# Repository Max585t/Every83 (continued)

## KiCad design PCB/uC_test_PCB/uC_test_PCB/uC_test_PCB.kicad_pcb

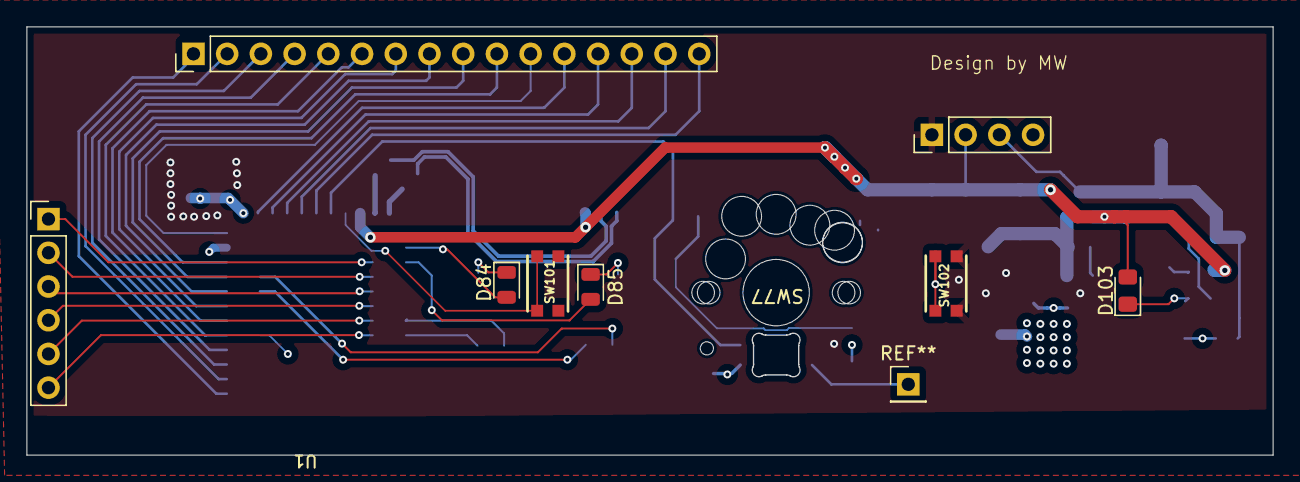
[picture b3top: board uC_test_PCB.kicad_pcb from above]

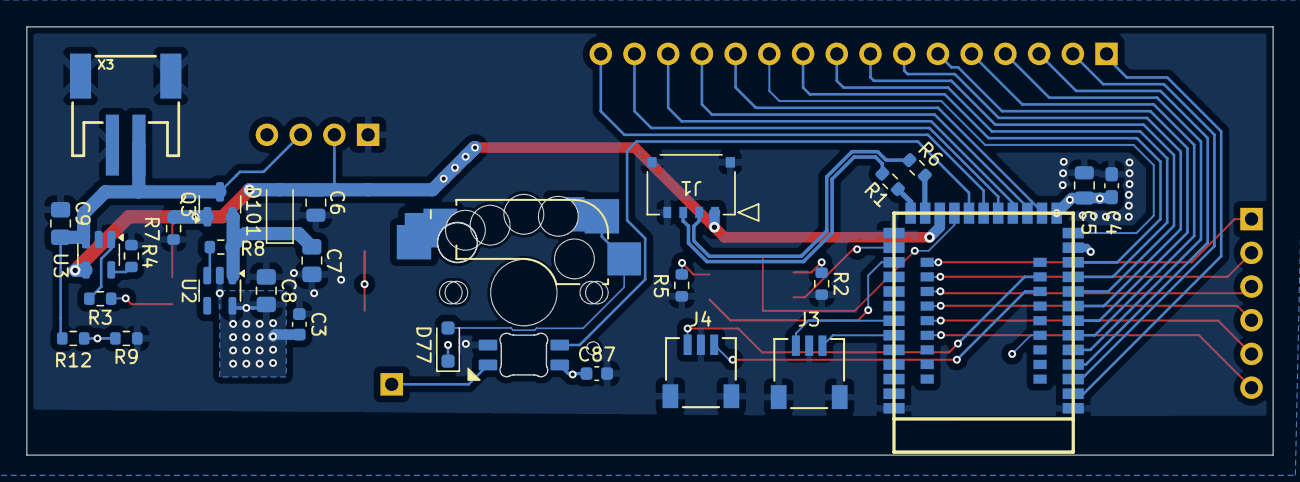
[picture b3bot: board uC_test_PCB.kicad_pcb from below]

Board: 4 copper layers, 93.9 x 32.3 mm, 34 parts (27 on the bottom side), 2 nets.

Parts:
C3: 0.1uF; C_0603_1608Metric
C4: 0.1uF; C_0603_1608Metric_Pad1.08x0.95mm_HandSolder
C5, C6: 10uF; C_0805_2012Metric
C7, C8, C9: 10uF; C_0805_2012Metric_Pad1.18x1.45mm_HandSolder
C87: C; C_0603_1608Metric
D77: D; D_SOD-323_HandSoldering
D84, D85: LED; LED_0805_2012Metric
D101: MBR120; D_SOD-123
D103: LED; D_0805_2012Metric_Pad1.15x1.40mm_HandSolder
J1: 781710004; CON_781710004
J3, J4: SM03B-SRSS-TB; CONN_SM03B-SRSS-TB_JST
Q3: DMG2305; SOT-23
R1, R6: 22R; R_0603_1608Metric
R2, R3, R5: 1K; R_0603_1608Metric
R4: 4.7K; R_0603_1608Metric
R7, R8, R9, R12: 100k; R_0603_1608Metric
SW77: gateron-ks27-choc-v1-mx-hotswap
SW101, SW102: KMR2; BTN_KMR2_4.6X2.8
U1: Core52840
U2: AP2112(3.3V); SOT-23-5
U3: MCP73831T-2ACI/OT; SOT-23-5
X3: JSTPH; JSTPH2

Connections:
3v3: C3.2, C4.2, C5.2, C8.2, C87.1, SW77.4 (VDD), U1.55 (VREF), U2.5 (OUT)
GND: C3.1, C4.1, C5.1, C6.1, C7.1, C8.1, C9.1, C87.2, J1.4, J1.5, J1.6, J3.2, J3.4, J3.5, J4.2, J4.4, J4.5, R2.2, R4.2, R5.2, R7.2, R9.2, SW77.6 (GND), SW102.A, SW102.A' (P1), U1.1 (GND), U1.32 (GND), U1.44 (GND), U2.2 (GND), U3.2 (VSS), X3.1, X3.NC1, X3.NC2

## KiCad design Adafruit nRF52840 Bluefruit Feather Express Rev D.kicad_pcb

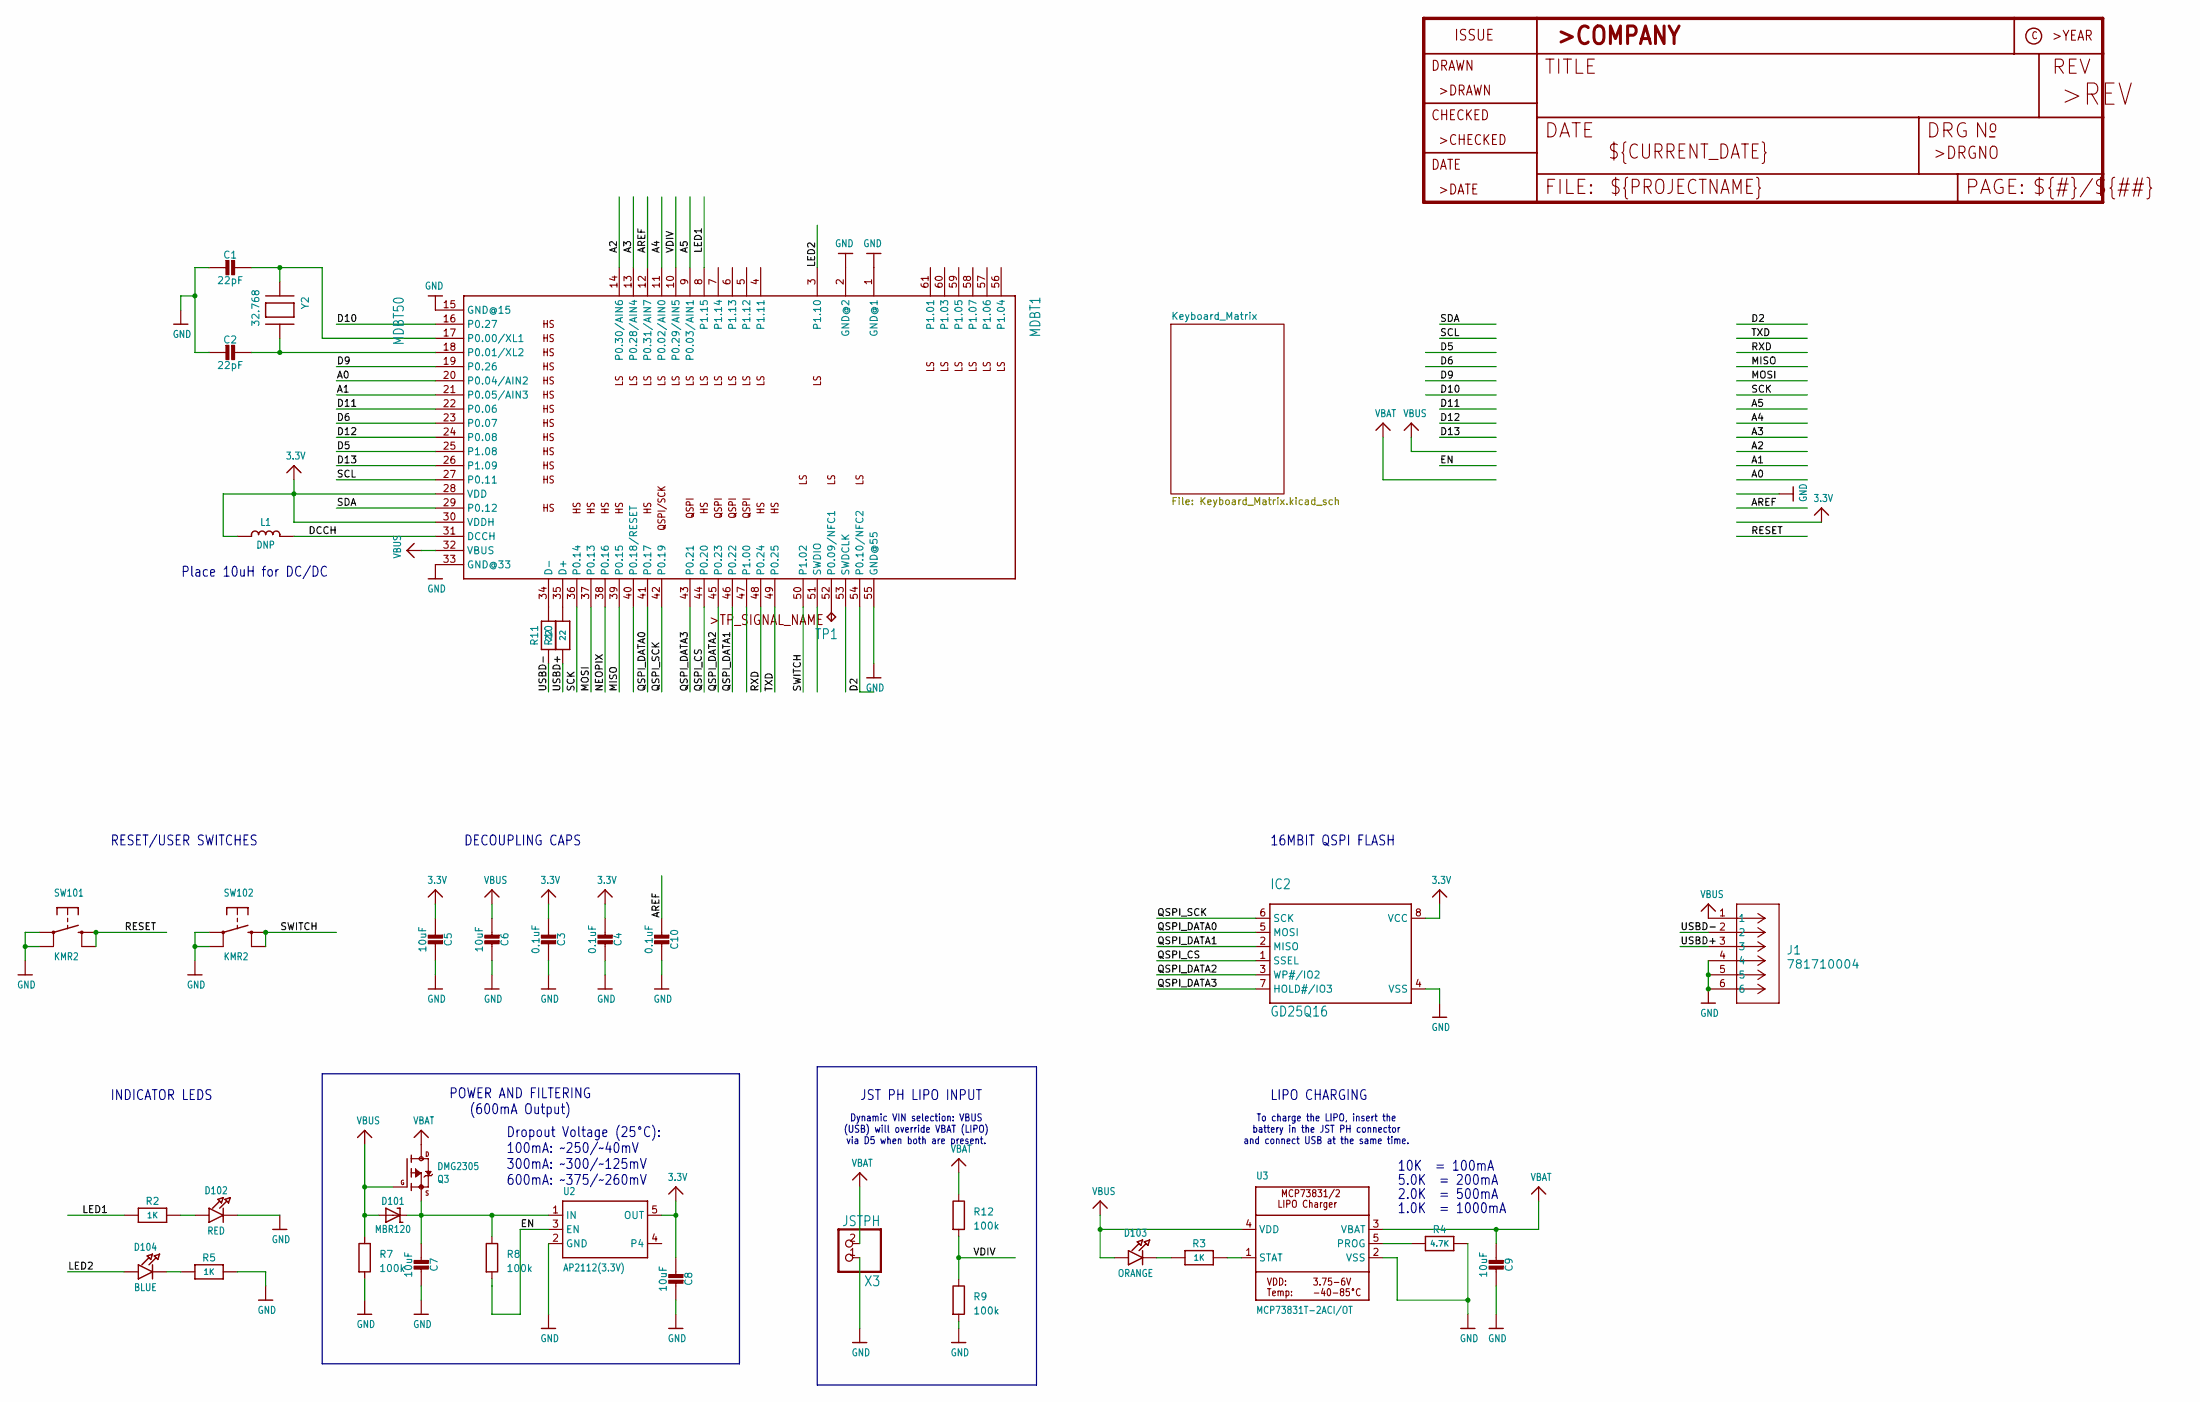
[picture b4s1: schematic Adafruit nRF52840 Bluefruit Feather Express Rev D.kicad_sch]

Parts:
C1, C2: 22pF; 0603-NO
C3, C4, C10: 0.1uF; 0603-NO
C5, C6, C7, C8, C9: 10uF; 0805-NO
D101: MBR120; SOD-123
D102: RED; CHIPLED_0805_NOOUTLINE
D103: ORANGE; CHIPLED_0805_NOOUTLINE
D104: BLUE; CHIPLED_0805_NOOUTLINE
IC2: GD25Q16; USON8
J1: 781710004; CON_781710004
L1: DNP; _0805MP
MDBT1: MDBT50
Q3: DMG2305; SOT23-R
R2, R3, R5: 1K; 0603-NO
R4: 4.7K; 0603-NO
R7, R8, R9, R12: 100k; R_0603_1608Metric
R10, R11: 22; 0603-NO
SW101, SW102: KMR2; BTN_KMR2_4.6X2.8
TP1: TPTP10R; TP10R
U2: AP2112(3.3V); SOT23-5
U3: MCP73831T-2ACI/OT; SOT23-5
X3: JSTPH; JSTPH2
Y2: 32.768; XTAL3215

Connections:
3.3V: C3.2, C4.2, C5.2, C8.2, IC2.8 (VCC), L1.1, MDBT1.28 (VDD), MDBT1.30 (VDDH), U2.5 (OUT); also elsewhere on the board
/A0: MDBT1.20 (P0.04/AIN2)
/A1: MDBT1.21 (P0.05/AIN3)
/A2: MDBT1.14 (P0.30/AIN6)
/A3: MDBT1.13 (P0.28/AIN4)
/A4: MDBT1.11 (P0.02/AIN0)
/A5: MDBT1.9 (P0.03/AIN1)
/AREF: C10.2, MDBT1.12 (P0.31/AIN7)
/D2: MDBT1.54 (P0.10/NFC2)
/D5: MDBT1.25 (P1.08)
/D6: MDBT1.23 (P0.07)
/D9: MDBT1.19 (P0.26)
/D10: MDBT1.16 (P0.27)
/D11: MDBT1.22 (P0.06)
/D12: MDBT1.24 (P0.08)
/D13: MDBT1.26 (P1.09)
/DCCH: L1.2, MDBT1.31 (DCCH)
/EN: R8.2, U2.3 (EN)
/LED1: MDBT1.8 (P1.15), R2.1
/LED2: D104.A, MDBT1.3 (P1.10)
/MISO: MDBT1.39 (P0.15)
/MOSI: MDBT1.37 (P0.13)
/NEOPIX: MDBT1.38 (P0.16)
/QSPI_CS: IC2.1 (SSEL), MDBT1.44 (P0.20)
/QSPI_DATA0: IC2.5 (MOSI), MDBT1.41 (P0.17)
/QSPI_DATA1: IC2.2 (MISO), MDBT1.46 (P0.22)
/QSPI_DATA2: IC2.3 (WP#/IO2), MDBT1.45 (P0.23)
/QSPI_DATA3: IC2.7 (HOLD#/IO3), MDBT1.43 (P0.21)
/QSPI_SCK: IC2.6 (SCK), MDBT1.42 (P0.19)
/RESET: SW101.B (S), SW101.B' (S1)
/RXD: MDBT1.48 (P0.24)
/SCK: MDBT1.36 (P0.14)
/SCL: MDBT1.27 (P0.11)
/SDA: MDBT1.29 (P0.12)
/SWITCH: MDBT1.50 (P1.02), SW102.B (S), SW102.B' (S1)
/TXD: MDBT1.49 (P0.25)
/USBD+: J1.3, R10.1
/USBD-: J1.2, R11.1
/VDIV: MDBT1.10 (P0.29/AIN5), R9.1, R12.2
GND: C1.2, C2.2, C3.1, C4.1, C5.1, C6.1, C7.1, C8.1, C9.1, C10.1, D102.C, IC2.4 (VSS), J1.4, J1.5, J1.6, MDBT1.1 (GND@1), MDBT1.2 (GND@2), MDBT1.15 (GND@15), MDBT1.33 (GND@33), MDBT1.55 (GND@55), R4.2, R5.2, R7.2, R9.2, SW101.A, SW101.A' (P1), SW102.A, SW102.A' (P1), U2.2 (GND), U3.2 (VSS), X3.1; also elsewhere on the board
unnamed: D102.A, R2.2
unnamed: D103.C, R3.1
unnamed: D104.C, R5.1
unnamed: MDBT1.35 (D+), R10.2
unnamed: MDBT1.34 (D-), R11.2
unnamed: C1.1, MDBT1.17 (P0.00/XL1), Y2.P$1
unnamed: C2.1, MDBT1.18 (P0.01/XL2), Y2.P$2
unnamed: MDBT1.52 (P0.09/NFC1), TP1.TP
unnamed: C7.2, D101.C, Q3.2 (S), R8.1, U2.1 (IN)
unnamed: R4.1, U3.5 (PROG)
unnamed: R3.2, U3.1 (STAT)
VBAT: C9.2, Q3.3 (D), R12.1, U3.3 (VBAT), X3.2
VBUS: C6.2, D101.A, D103.A, J1.1, MDBT1.32 (VBUS), Q3.1 (G), R7.1, U3.4 (VDD)

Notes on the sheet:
Dynamic VIN selection: VBUS (USB) will override VBAT (LIPO) via D5 when both are present.
To charge the LIPO, insert the battery in the JST PH connector and connect USB at the same time.
POWER AND FILTERING (600mA Output)
1.0K = 1000mA
Place 10uH for DC/DC
INDICATOR LEDS
5.0K = 200mA
JST PH LIPO INPUT
LIPO CHARGING
RESET/USER SWITCHES
10K = 100mA
2.0K = 500mA
16MBIT QSPI FLASH
Dropout Voltage (25°C): 100mA: ~250/~40mV 300mA: ~300/~125mV 600mA: ~375/~260mV
DECOUPLING CAPS

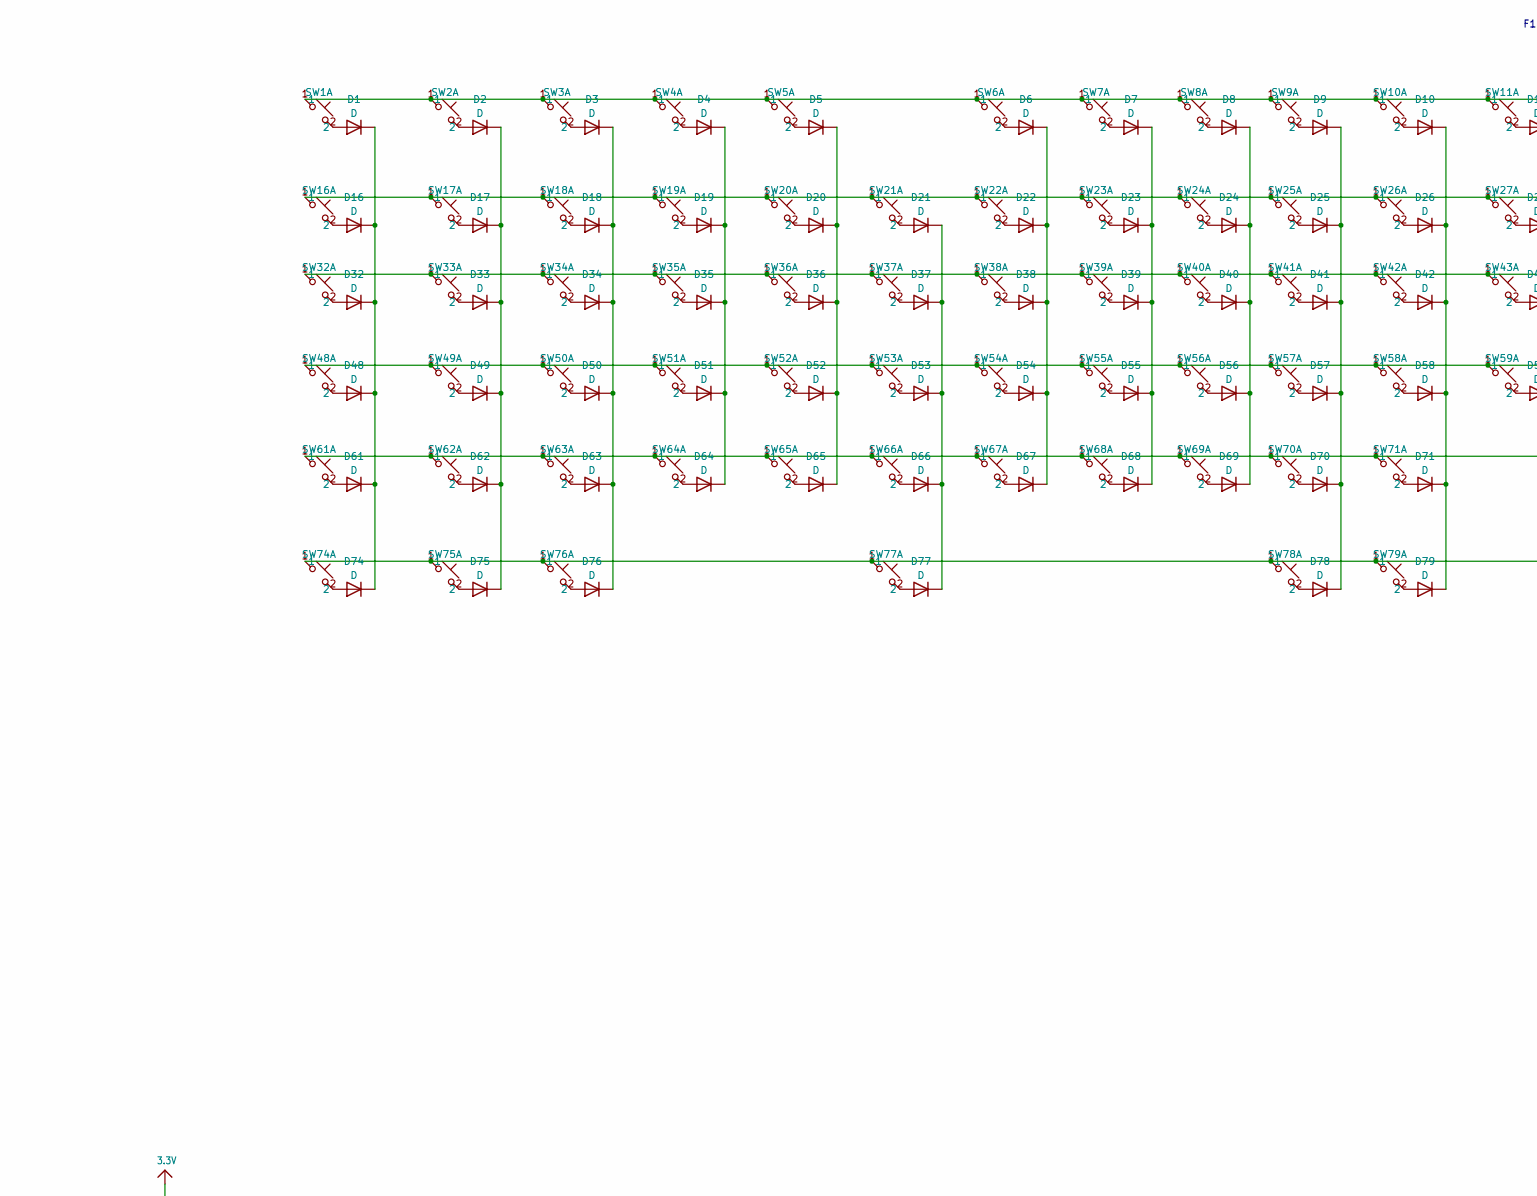
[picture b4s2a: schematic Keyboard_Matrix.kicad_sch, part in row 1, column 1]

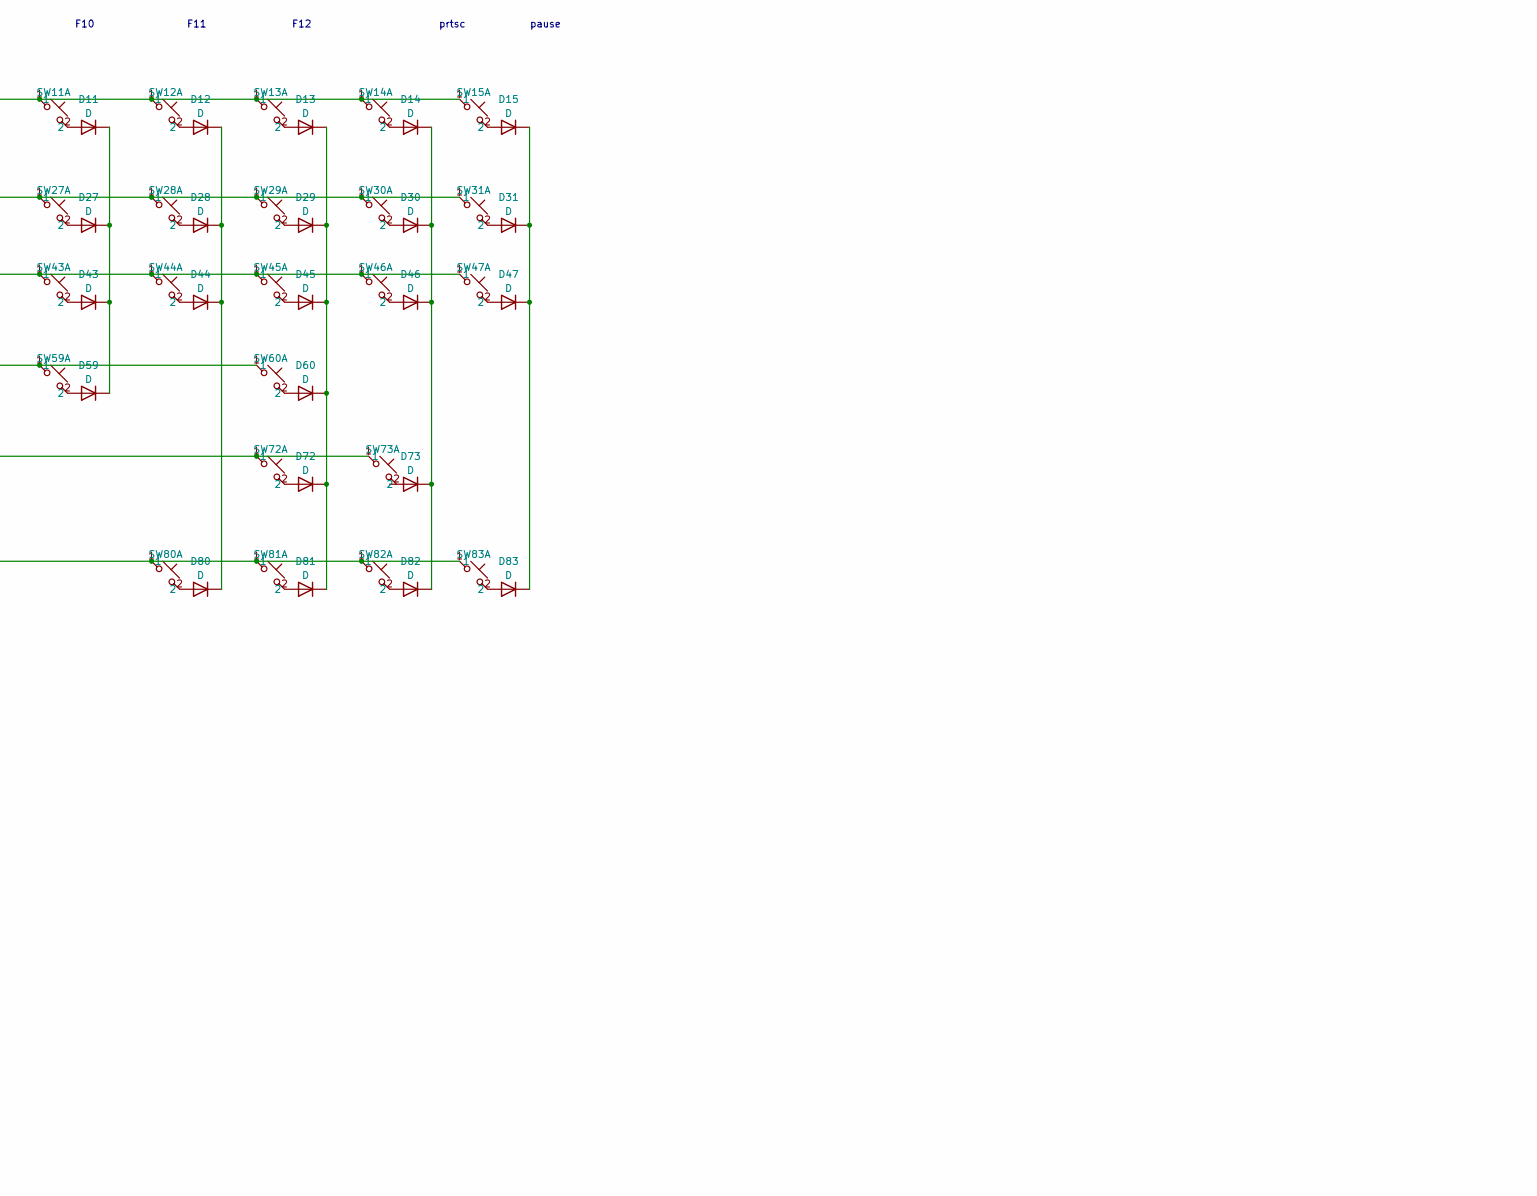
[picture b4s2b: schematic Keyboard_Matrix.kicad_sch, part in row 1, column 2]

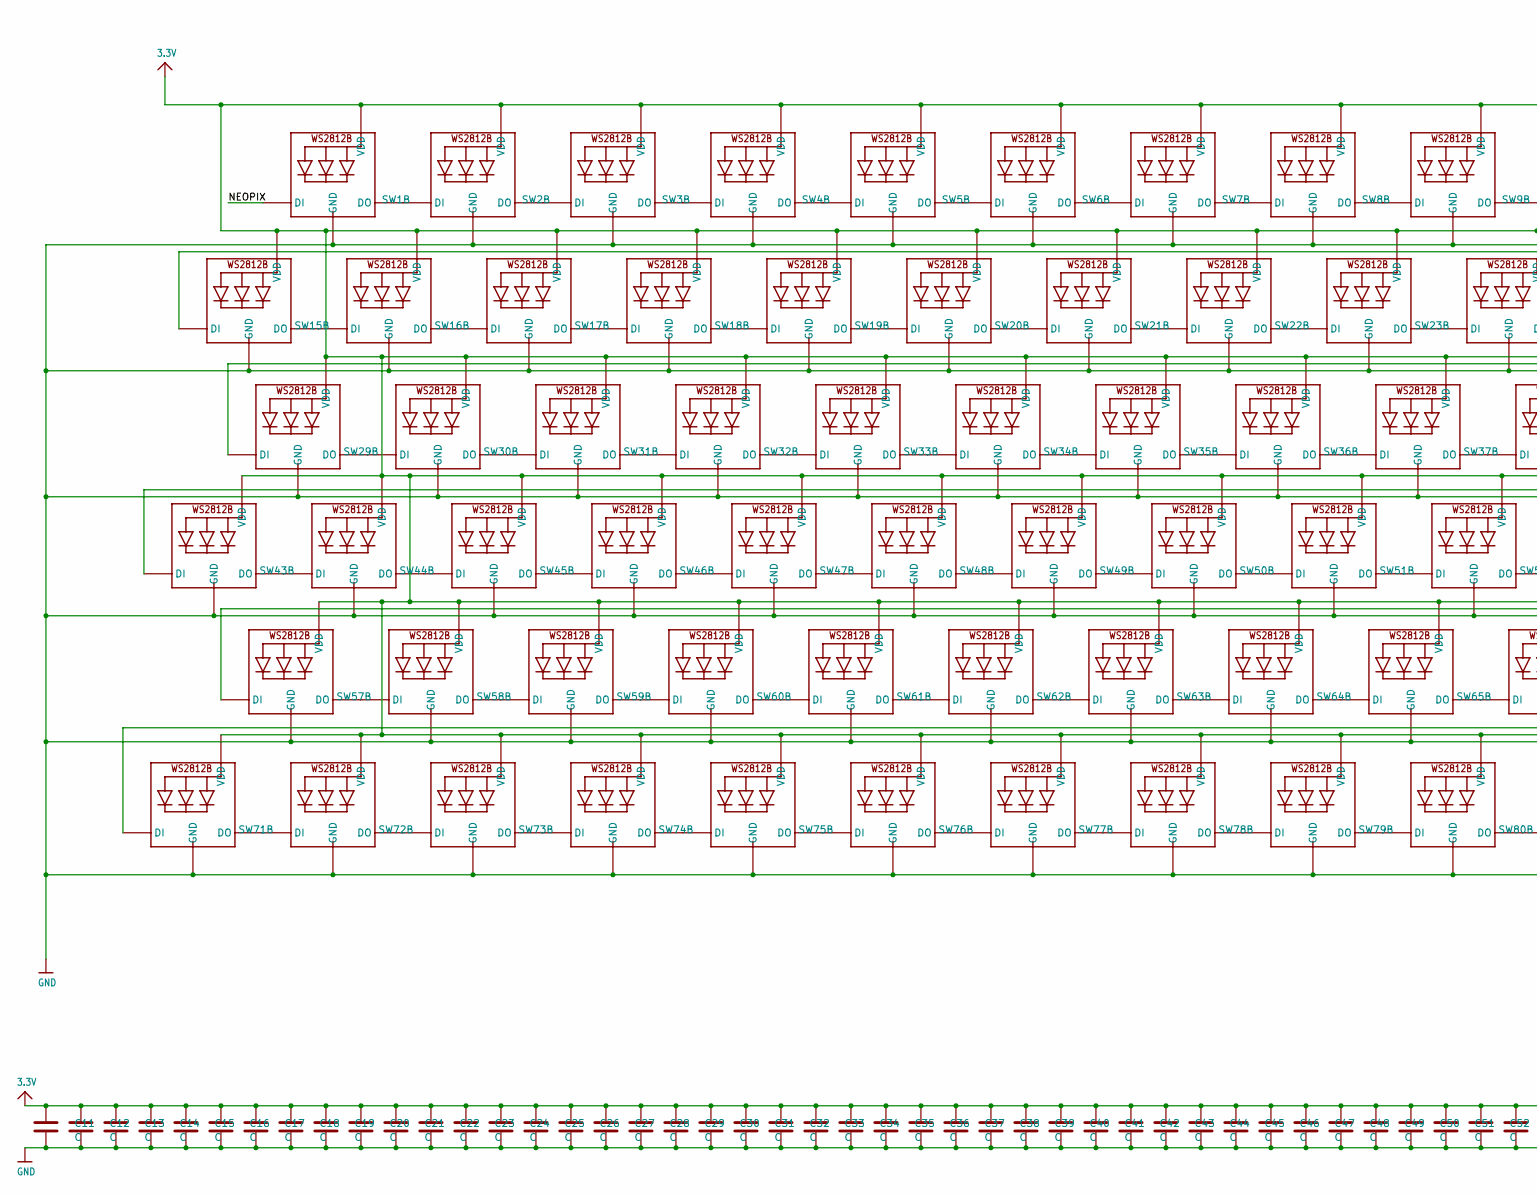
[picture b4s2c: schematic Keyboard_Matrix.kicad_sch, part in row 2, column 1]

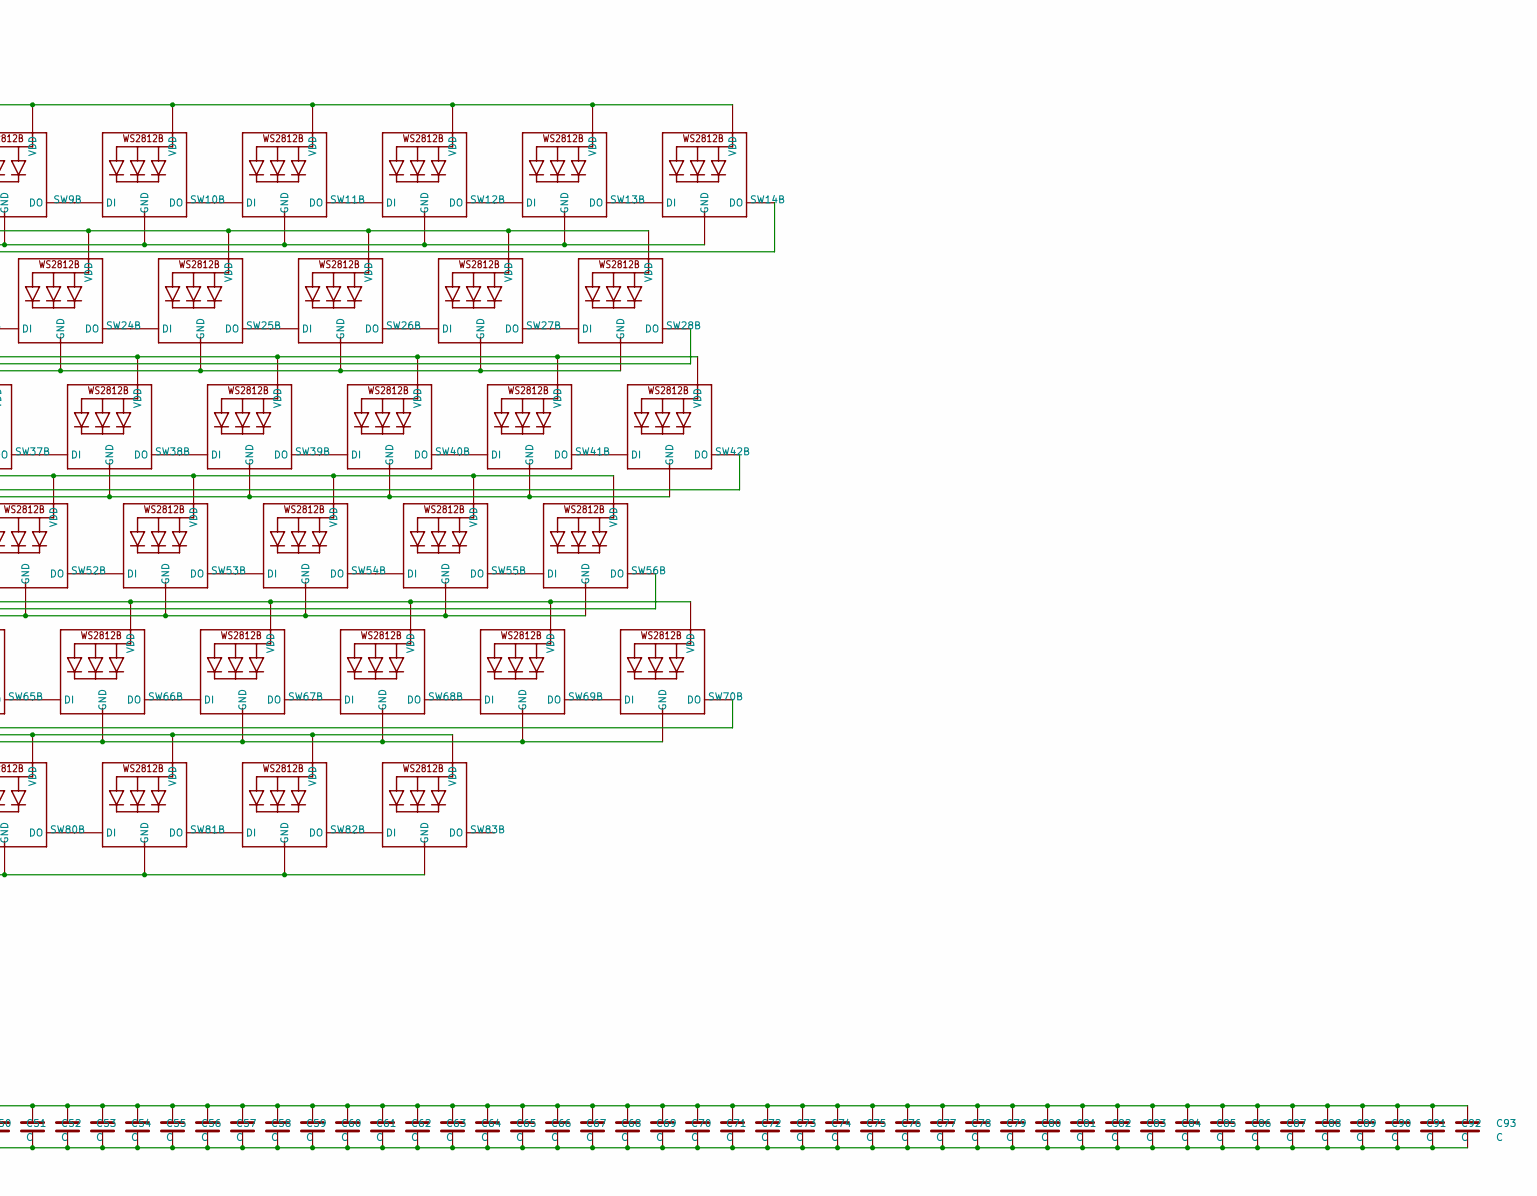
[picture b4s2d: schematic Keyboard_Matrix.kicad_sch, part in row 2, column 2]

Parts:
C11, C12, C13, C14, C15, C16, C17, C18, C19, C20, C21, C22, C23, C24, C25, C26, C27, C28, C29, C30, C31, C32, C33, C34, C35, C36, C37, C38, C39, C40, C41, C42, C43, C44, C45, C46, C47, C48, C49, C50, C51, C52, C53, C54, C55, C56, C57, C58, C59, C60, C61, C62, C63, C64, C65, C66, C67, C68, C69, C70, C71, C72, C73, C74, C75, C76, C77, C78, C79, C80, C81, C82, C83, C84, C85, C86, C87, C88, C89, C90, C91, C92, C93: C; C_0603_1608Metric
D1, D2, D3, D4, D5, D6, D7, D8, D9, D10, D11, D12, D13, D14, D15, D16, D17, D18, D19, D20, D21, D22, D23, D24, D25, D26, D27, D28, D29, D30, D31, D32, D33, D34, D35, D36, D37, D38, D39, D40, D41, D42, D43, D44, D45, D46, D47, D48, D49, D50, D51, D52, D53, D54, D55, D56, D57, D58, D59, D60, D61, D62, D63, D64, D65, D66, D67, D68, D69, D70, D71, D72, D73, D74, D75, D76, D77, D78, D79, D80, D81, D82, D83: D; D_SOD-323_HandSoldering
SW1, SW2, SW3, SW4, SW5, SW6, SW7, SW8, SW9, SW10, SW11, SW12, SW13, SW14, SW15, SW16, SW17, SW18, SW19, SW20, SW21, SW22, SW23, SW24, SW25, SW26, SW27, SW28, SW29, SW30, SW31, SW32, SW33, SW34, SW35, SW36, SW37, SW38, SW39, SW40, SW41, SW42, SW43, SW44, SW45, SW46, SW47, SW48, SW49, SW50, SW51, SW52, SW53, SW54, SW55, SW56, SW57, SW58, SW59, SW60, SW61, SW62, SW63, SW64, SW65, SW66, SW67, SW68, SW69, SW70, SW71, SW72, SW73, SW74, SW75, SW76, SW77, SW78, SW79, SW80, SW81, SW82, SW83: gateron-ks27-choc-v1-mx-hotswap

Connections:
3.3V: C11.1, C12.1, C13.1, C14.1, C15.1, C16.1, C17.1, C18.1, C19.1, C20.1, C21.1, C22.1, C23.1, C24.1, C25.1, C26.1, C27.1, C28.1, C29.1, C30.1, C31.1, C32.1, C33.1, C34.1, C35.1, C36.1, C37.1, C38.1, C39.1, C40.1, C41.1, C42.1, C43.1, C44.1, C45.1, C46.1, C47.1, C48.1, C49.1, C50.1, C51.1, C52.1, C53.1, C54.1, C55.1, C56.1, C57.1, C58.1, C59.1, C60.1, C61.1, C62.1, C63.1, C64.1, C65.1, C66.1, C67.1, C68.1, C69.1, C70.1, C71.1, C72.1, C73.1, C74.1, C75.1, C76.1, C77.1, C78.1, C79.1, C80.1, C81.1, C82.1, C83.1, C84.1, C85.1, C86.1, C87.1, C88.1, C89.1, C90.1, C91.1, C92.1, C93.1, SW1.4 (VDD), SW2.4 (VDD), SW3.4 (VDD), SW4.4 (VDD), SW5.4 (VDD), SW6.4 (VDD), SW7.4 (VDD), SW8.4 (VDD), SW9.4 (VDD), SW10.4 (VDD), SW11.4 (VDD), SW12.4 (VDD), SW13.4 (VDD), SW14.4 (VDD), SW15.4 (VDD), SW16.4 (VDD), SW17.4 (VDD), SW18.4 (VDD), SW19.4 (VDD), SW20.4 (VDD), SW21.4 (VDD), SW22.4 (VDD), SW23.4 (VDD), SW24.4 (VDD), SW25.4 (VDD), SW26.4 (VDD), SW27.4 (VDD), SW28.4 (VDD), SW29.4 (VDD), SW30.4 (VDD), SW31.4 (VDD), SW32.4 (VDD), SW33.4 (VDD), SW34.4 (VDD), SW35.4 (VDD), SW36.4 (VDD), SW37.4 (VDD), SW38.4 (VDD), SW39.4 (VDD), SW40.4 (VDD), SW41.4 (VDD), SW42.4 (VDD), SW43.4 (VDD), SW44.4 (VDD), SW45.4 (VDD), SW46.4 (VDD), SW47.4 (VDD), SW48.4 (VDD), SW49.4 (VDD), SW50.4 (VDD), SW51.4 (VDD), SW52.4 (VDD), SW53.4 (VDD), SW54.4 (VDD), SW55.4 (VDD), SW56.4 (VDD), SW57.4 (VDD), SW58.4 (VDD), SW59.4 (VDD), SW60.4 (VDD), SW61.4 (VDD), SW62.4 (VDD), SW63.4 (VDD), SW64.4 (VDD), SW65.4 (VDD), SW66.4 (VDD), SW67.4 (VDD), SW68.4 (VDD), SW69.4 (VDD), SW70.4 (VDD), SW71.4 (VDD), SW72.4 (VDD), SW73.4 (VDD), SW74.4 (VDD), SW75.4 (VDD), SW76.4 (VDD), SW77.4 (VDD), SW78.4 (VDD), SW79.4 (VDD), SW80.4 (VDD), SW81.4 (VDD), SW82.4 (VDD), SW83.4 (VDD); also elsewhere on the board
/Keyboard_Matrix/NEOPIX: SW1.3 (DI)
GND: C11.2, C12.2, C13.2, C14.2, C15.2, C16.2, C17.2, C18.2, C19.2, C20.2, C21.2, C22.2, C23.2, C24.2, C25.2, C26.2, C27.2, C28.2, C29.2, C30.2, C31.2, C32.2, C33.2, C34.2, C35.2, C36.2, C37.2, C38.2, C39.2, C40.2, C41.2, C42.2, C43.2, C44.2, C45.2, C46.2, C47.2, C48.2, C49.2, C50.2, C51.2, C52.2, C53.2, C54.2, C55.2, C56.2, C57.2, C58.2, C59.2, C60.2, C61.2, C62.2, C63.2, C64.2, C65.2, C66.2, C67.2, C68.2, C69.2, C70.2, C71.2, C72.2, C73.2, C74.2, C75.2, C76.2, C77.2, C78.2, C79.2, C80.2, C81.2, C82.2, C83.2, C84.2, C85.2, C86.2, C87.2, C88.2, C89.2, C90.2, C91.2, C92.2, C93.2, SW1.6 (GND), SW2.6 (GND), SW3.6 (GND), SW4.6 (GND), SW5.6 (GND), SW6.6 (GND), SW7.6 (GND), SW8.6 (GND), SW9.6 (GND), SW10.6 (GND), SW11.6 (GND), SW12.6 (GND), SW13.6 (GND), SW14.6 (GND), SW15.6 (GND), SW16.6 (GND), SW17.6 (GND), SW18.6 (GND), SW19.6 (GND), SW20.6 (GND), SW21.6 (GND), SW22.6 (GND), SW23.6 (GND), SW24.6 (GND), SW25.6 (GND), SW26.6 (GND), SW27.6 (GND), SW28.6 (GND), SW29.6 (GND), SW30.6 (GND), SW31.6 (GND), SW32.6 (GND), SW33.6 (GND), SW34.6 (GND), SW35.6 (GND), SW36.6 (GND), SW37.6 (GND), SW38.6 (GND), SW39.6 (GND), SW40.6 (GND), SW41.6 (GND), SW42.6 (GND), SW43.6 (GND), SW44.6 (GND), SW45.6 (GND), SW46.6 (GND), SW47.6 (GND), SW48.6 (GND), SW49.6 (GND), SW50.6 (GND), SW51.6 (GND), SW52.6 (GND), SW53.6 (GND), SW54.6 (GND), SW55.6 (GND), SW56.6 (GND), SW57.6 (GND), SW58.6 (GND), SW59.6 (GND), SW60.6 (GND), SW61.6 (GND), SW62.6 (GND), SW63.6 (GND), SW64.6 (GND), SW65.6 (GND), SW66.6 (GND), SW67.6 (GND), SW68.6 (GND), SW69.6 (GND), SW70.6 (GND), SW71.6 (GND), SW72.6 (GND), SW73.6 (GND), SW74.6 (GND), SW75.6 (GND), SW76.6 (GND), SW77.6 (GND), SW78.6 (GND), SW79.6 (GND), SW80.6 (GND), SW81.6 (GND), SW82.6 (GND), SW83.6 (GND); also elsewhere on the board
unnamed: D1.2 (A), SW1.2
unnamed: D1.1 (K), D16.1 (K), D32.1 (K), D48.1 (K), D61.1 (K), D74.1 (K)
unnamed: D2.2 (A), SW2.2
unnamed: D3.2 (A), SW3.2
unnamed: D4.2 (A), SW4.2
unnamed: D5.2 (A), SW5.2
unnamed: D6.2 (A), SW6.2
unnamed: D7.2 (A), SW7.2
unnamed: D8.2 (A), SW8.2
unnamed: D9.2 (A), SW9.2
unnamed: D10.2 (A), SW10.2
unnamed: D10.1 (K), D26.1 (K), D42.1 (K), D58.1 (K), D71.1 (K), D79.1 (K)
unnamed: D11.2 (A), SW11.2
unnamed: D11.1 (K), D27.1 (K), D43.1 (K), D59.1 (K)
unnamed: D12.2 (A), SW12.2
unnamed: D12.1 (K), D28.1 (K), D44.1 (K), D80.1 (K)
unnamed: D13.2 (A), SW13.2
unnamed: D13.1 (K), D29.1 (K), D45.1 (K), D60.1 (K), D72.1 (K), D81.1 (K)
unnamed: D14.2 (A), SW14.2
unnamed: D14.1 (K), D30.1 (K), D46.1 (K), D73.1 (K), D82.1 (K)
unnamed: D15.2 (A), SW15.2
unnamed: D15.1 (K), D31.1 (K), D47.1 (K), D83.1 (K)
unnamed: D16.2 (A), SW16.2
unnamed: D17.2 (A), SW17.2
unnamed: D2.1 (K), D17.1 (K), D33.1 (K), D49.1 (K), D62.1 (K), D75.1 (K)
unnamed: D18.2 (A), SW18.2
unnamed: D3.1 (K), D18.1 (K), D34.1 (K), D50.1 (K), D63.1 (K), D76.1 (K)
unnamed: D19.2 (A), SW19.2
unnamed: D4.1 (K), D19.1 (K), D35.1 (K), D51.1 (K), D64.1 (K)
unnamed: D20.2 (A), SW20.2
unnamed: D5.1 (K), D20.1 (K), D36.1 (K), D52.1 (K), D65.1 (K)
unnamed: D21.2 (A), SW21.2
unnamed: D21.1 (K), D37.1 (K), D53.1 (K), D66.1 (K), D77.1 (K)
unnamed: D22.2 (A), SW22.2
unnamed: D6.1 (K), D22.1 (K), D38.1 (K), D54.1 (K), D67.1 (K)
unnamed: D23.2 (A), SW23.2
unnamed: D7.1 (K), D23.1 (K), D39.1 (K), D55.1 (K), D68.1 (K)
unnamed: D24.2 (A), SW24.2
unnamed: D8.1 (K), D24.1 (K), D40.1 (K), D56.1 (K), D69.1 (K)
unnamed: D25.2 (A), SW25.2
unnamed: D9.1 (K), D25.1 (K), D41.1 (K), D57.1 (K), D70.1 (K), D78.1 (K)
unnamed: D26.2 (A), SW26.2
unnamed: D27.2 (A), SW27.2
unnamed: D28.2 (A), SW28.2
unnamed: D29.2 (A), SW29.2
unnamed: D30.2 (A), SW30.2
unnamed: D31.2 (A), SW31.2
unnamed: D32.2 (A), SW32.2
unnamed: D33.2 (A), SW33.2
unnamed: D34.2 (A), SW34.2
unnamed: D35.2 (A), SW35.2
unnamed: D36.2 (A), SW36.2
unnamed: D37.2 (A), SW37.2
unnamed: D38.2 (A), SW38.2
unnamed: D39.2 (A), SW39.2
unnamed: D40.2 (A), SW40.2
unnamed: D41.2 (A), SW41.2
unnamed: D42.2 (A), SW42.2
unnamed: D43.2 (A), SW43.2
unnamed: D44.2 (A), SW44.2
unnamed: D45.2 (A), SW45.2
unnamed: D46.2 (A), SW46.2
unnamed: D47.2 (A), SW47.2
unnamed: D48.2 (A), SW48.2
unnamed: D49.2 (A), SW49.2
unnamed: D50.2 (A), SW50.2
unnamed: D51.2 (A), SW51.2
unnamed: D52.2 (A), SW52.2
unnamed: D53.2 (A), SW53.2
unnamed: D54.2 (A), SW54.2
unnamed: D55.2 (A), SW55.2
unnamed: D56.2 (A), SW56.2
unnamed: D57.2 (A), SW57.2
unnamed: D58.2 (A), SW58.2
unnamed: D59.2 (A), SW59.2
unnamed: D60.2 (A), SW60.2
unnamed: D61.2 (A), SW61.2
unnamed: D62.2 (A), SW62.2
unnamed: D63.2 (A), SW63.2
unnamed: D64.2 (A), SW64.2
unnamed: D65.2 (A), SW65.2
unnamed: D66.2 (A), SW66.2
unnamed: D67.2 (A), SW67.2
unnamed: D68.2 (A), SW68.2
unnamed: D69.2 (A), SW69.2
unnamed: D70.2 (A), SW70.2
unnamed: D71.2 (A), SW71.2
unnamed: D72.2 (A), SW72.2
unnamed: D73.2 (A), SW73.2
unnamed: D74.2 (A), SW74.2
unnamed: D75.2 (A), SW75.2
unnamed: D76.2 (A), SW76.2
unnamed: D77.2 (A), SW77.2
unnamed: D78.2 (A), SW78.2
unnamed: D79.2 (A), SW79.2
unnamed: D80.2 (A), SW80.2
unnamed: D81.2 (A), SW81.2
unnamed: D82.2 (A), SW82.2
unnamed: D83.2 (A), SW83.2
unnamed: SW1.1, SW2.1, SW3.1, SW4.1, SW5.1, SW6.1, SW7.1, SW8.1, SW9.1, SW10.1, SW11.1, SW12.1, SW13.1, SW14.1, SW15.1
unnamed: SW1.5 (DO), SW2.3 (DI)
unnamed: SW2.5 (DO), SW3.3 (DI)
unnamed: SW3.5 (DO), SW4.3 (DI)
unnamed: SW4.5 (DO), SW5.3 (DI)
unnamed: SW5.5 (DO), SW6.3 (DI)
unnamed: SW6.5 (DO), SW7.3 (DI)
unnamed: SW7.5 (DO), SW8.3 (DI)
unnamed: SW8.5 (DO), SW9.3 (DI)
unnamed: SW9.5 (DO), SW10.3 (DI)
unnamed: SW10.5 (DO), SW11.3 (DI)
unnamed: SW11.5 (DO), SW12.3 (DI)
unnamed: SW12.5 (DO), SW13.3 (DI)
unnamed: SW13.5 (DO), SW14.3 (DI)
unnamed: SW14.5 (DO), SW15.3 (DI)
unnamed: SW15.5 (DO), SW16.3 (DI)
unnamed: SW16.1, SW17.1, SW18.1, SW19.1, SW20.1, SW21.1, SW22.1, SW23.1, SW24.1, SW25.1, SW26.1, SW27.1, SW28.1, SW29.1, SW30.1, SW31.1
unnamed: SW16.5 (DO), SW17.3 (DI)
unnamed: SW17.5 (DO), SW18.3 (DI)
unnamed: SW18.5 (DO), SW19.3 (DI)
unnamed: SW19.5 (DO), SW20.3 (DI)
unnamed: SW20.5 (DO), SW21.3 (DI)
unnamed: SW21.5 (DO), SW22.3 (DI)
unnamed: SW22.5 (DO), SW23.3 (DI)
unnamed: SW23.5 (DO), SW24.3 (DI)
unnamed: SW24.5 (DO), SW25.3 (DI)
unnamed: SW25.5 (DO), SW26.3 (DI)
unnamed: SW26.5 (DO), SW27.3 (DI)
unnamed: SW27.5 (DO), SW28.3 (DI)
unnamed: SW28.5 (DO), SW29.3 (DI)
unnamed: SW29.5 (DO), SW30.3 (DI)
unnamed: SW30.5 (DO), SW31.3 (DI)
unnamed: SW31.5 (DO), SW32.3 (DI)
unnamed: SW32.1, SW33.1, SW34.1, SW35.1, SW36.1, SW37.1, SW38.1, SW39.1, SW40.1, SW41.1, SW42.1, SW43.1, SW44.1, SW45.1, SW46.1, SW47.1
unnamed: SW32.5 (DO), SW33.3 (DI)
unnamed: SW33.5 (DO), SW34.3 (DI)
unnamed: SW34.5 (DO), SW35.3 (DI)
unnamed: SW35.5 (DO), SW36.3 (DI)
unnamed: SW36.5 (DO), SW37.3 (DI)
unnamed: SW37.5 (DO), SW38.3 (DI)
unnamed: SW38.5 (DO), SW39.3 (DI)
unnamed: SW39.5 (DO), SW40.3 (DI)
unnamed: SW40.5 (DO), SW41.3 (DI)
unnamed: SW41.5 (DO), SW42.3 (DI)
unnamed: SW42.5 (DO), SW43.3 (DI)
unnamed: SW43.5 (DO), SW44.3 (DI)
unnamed: SW44.5 (DO), SW45.3 (DI)
unnamed: SW45.5 (DO), SW46.3 (DI)
unnamed: SW46.5 (DO), SW47.3 (DI)
unnamed: SW47.5 (DO), SW48.3 (DI)
unnamed: SW48.1, SW49.1, SW50.1, SW51.1, SW52.1, SW53.1, SW54.1, SW55.1, SW56.1, SW57.1, SW58.1, SW59.1, SW60.1
unnamed: SW48.5 (DO), SW49.3 (DI)
unnamed: SW49.5 (DO), SW50.3 (DI)
unnamed: SW50.5 (DO), SW51.3 (DI)
unnamed: SW51.5 (DO), SW52.3 (DI)
unnamed: SW52.5 (DO), SW53.3 (DI)
unnamed: SW53.5 (DO), SW54.3 (DI)
unnamed: SW54.5 (DO), SW55.3 (DI)
unnamed: SW55.5 (DO), SW56.3 (DI)
unnamed: SW56.5 (DO), SW57.3 (DI)
unnamed: SW57.5 (DO), SW58.3 (DI)
unnamed: SW58.5 (DO), SW59.3 (DI)
unnamed: SW59.5 (DO), SW60.3 (DI)
unnamed: SW60.5 (DO), SW61.3 (DI)
unnamed: SW61.1, SW62.1, SW63.1, SW64.1, SW65.1, SW66.1, SW67.1, SW68.1, SW69.1, SW70.1, SW71.1, SW72.1, SW73.1
unnamed: SW61.5 (DO), SW62.3 (DI)
unnamed: SW62.5 (DO), SW63.3 (DI)
unnamed: SW63.5 (DO), SW64.3 (DI)
unnamed: SW64.5 (DO), SW65.3 (DI)
unnamed: SW65.5 (DO), SW66.3 (DI)
unnamed: SW66.5 (DO), SW67.3 (DI)
unnamed: SW67.5 (DO), SW68.3 (DI)
unnamed: SW68.5 (DO), SW69.3 (DI)
unnamed: SW69.5 (DO), SW70.3 (DI)
unnamed: SW70.5 (DO), SW71.3 (DI)
unnamed: SW71.5 (DO), SW72.3 (DI)
unnamed: SW72.5 (DO), SW73.3 (DI)
unnamed: SW73.5 (DO), SW74.3 (DI)
unnamed: SW74.1, SW75.1, SW76.1, SW77.1, SW78.1, SW79.1, SW80.1, SW81.1, SW82.1, SW83.1
unnamed: SW74.5 (DO), SW75.3 (DI)
unnamed: SW75.5 (DO), SW76.3 (DI)
unnamed: SW76.5 (DO), SW77.3 (DI)
unnamed: SW77.5 (DO), SW78.3 (DI)
unnamed: SW78.5 (DO), SW79.3 (DI)
unnamed: SW79.5 (DO), SW80.3 (DI)
unnamed: SW80.5 (DO), SW81.3 (DI)
unnamed: SW81.5 (DO), SW82.3 (DI)
unnamed: SW82.5 (DO), SW83.3 (DI)

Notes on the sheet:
F10
prtsc
F12
pause
F11

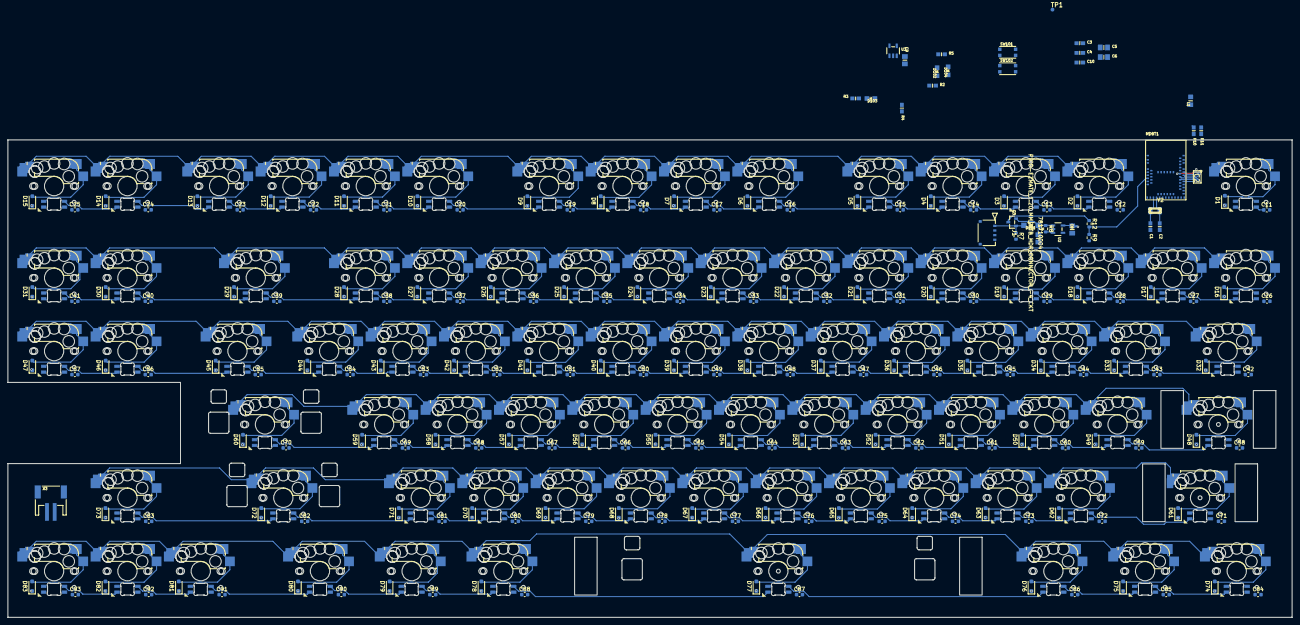
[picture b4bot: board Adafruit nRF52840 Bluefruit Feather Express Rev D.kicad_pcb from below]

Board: 4 copper layers, 333.6 x 124.0 mm, 287 parts (202 on the bottom side), 218 nets.

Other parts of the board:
gateron_stabs: gateron-ks57-2U
gateron_stabs#2: gateron-ks57-2U

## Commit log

2023-08-25 work
2023-08-26 Change folder structure
2023-08-26 add gitignore
2023-08-26 add backups to gitignore
2023-08-26 Add plates
2023-09-15 plate wip
2023-09-18 Small work
2023-09-19 removed bad diodes
    TODO: rotate good diodes
2023-09-20 work on matrix
2023-09-20 small work done
2023-09-22 Add stabs tester gerbers
2023-09-25 add kicad project for stab tester as zip
2023-10-03 work on keyboard and add single switch pcb
2023-10-14 add keycaps
2023-10-26 Add 3d models
2023-10-27 Move stuff around and create seperate kicad project for plate
2023-11-11 update footprint
2023-11-13 small updates
2023-11-15 Finalize plate layout
    As to whether or not to copper fill, yet to be determined
2023-11-16 Finished wiring diodes
2023-11-16 Make new stabilizer tester pcb
2023-12-15 voltage regulator
2023-12-21 Redo microcontroller layout
2023-12-22 Columns
2023-12-23 update matrix nets and add swd footprint
2024-01-01 update stabilizer tester pcb
2024-01-01 Matrix work
2024-02-02 update stab tester
2024-02-13 Footprint should be correct
2024-02-17 small changes to stab tester
2024-02-23 Fix stab footprint
2024-03-15 Kicad 8 and rotate the usb port
2024-03-23 Small work, moved the micro controller
    Need to update the programming pins and add UART
2024-03-25 Some more matrix work
2024-03-25 more small matrix work
2024-03-25 more matrix work
2024-03-28 Matrix should be done now
2024-03-28 missed something
2024-04-02 small changes
2024-04-10 swap micro
2024-04-11 Update the microcontroller footprint
2024-04-12 More work done
2024-04-17 Just need to run DRC now
2024-04-18 silkscreen changes
2024-04-18 make a uC test pcb
2024-04-19 small changes to test pcb
2024-04-19 uC test pcb done
2024-04-25 change battery connector
2024-04-29 Test pcb
2024-04-29 cuttout
2024-05-02 add breakout wires
2024-05-14 update the plate dimensions
2024-06-18 power switch pcb
2024-06-19 add power switch
2024-06-23 small changes - probably wont use
2024-06-24 smol changes
2024-07-03 Switch_LED_daughter_board done
2024-07-05 small changes to UX for charging
2024-07-08 change plate mounting style
2024-07-09 Change the layout of the power section
2024-07-12 small changes, place some components. Need to fix usb wiring
2024-07-17 update stab tester pbc
2024-07-18 Making some good progress
2024-08-01 Finished Switch PCB - Almost done with Keyboard (Need to fix 3v3 and GND)
2024-08-02 PCB is done, still need to do silkscreen
2024-09-06 add leds to pcb
2024-09-10 move the lights to main pcb
2024-09-11 small changes to led
2024-09-19 Oh Lawd he makin changes
2024-10-09 update neopixel power plane
2024-10-10 Moved the battery charger circuit
2024-10-11 Worked on the layout, not sure its good
2024-10-12 small changes in the right direction
2024-10-14 More work done. getting closer
2024-10-22 ROW 5 NOT FULLY CONNECTED
2024-10-31 Finished but need to change via size cause mooney
2024-11-14 updating VIA size
2024-12-09 PCB is finished
2025-01-31 Power switch done
2025-02-04 Closed the file
2025-03-12 Should be good now
2025-03-17 update silkscreen
2025-03-18 Update vias
2025-04-30 Removing neopixels WIP
2025-05-16 add white leds
2025-05-23 moved some resistors
2025-05-25 move resistors
2025-06-01 led routing done, vias need to be done
2025-06-06 pcb done
2025-06-19 removed pin headers
2025-09-03 Changed battery managment IC and LDO
2025-09-18 Orginizing and small work done
2025-09-19 Work done
2025-10-28 Work on Power Switch
2025-11-09 Add power switch connector to main board
2026-02-10 Add boost regulator for LEDs
2026-04-13 PCB Finished
2026-04-14 Update LED resistor value
